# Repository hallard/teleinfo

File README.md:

Update 12.10.2021: Moved APIKEY from url to Authorization Header

Repository dédié à la Téléinformation
=====================================

Ce dossier à la base était pour le programme téléinfo broadcast et emoncms, mais il est devenu au fur et à mesure un peu le fourre tout de mes projets concernant la téléinformation.
Dorénavant, je crée des repos séparés pour les nouveaux projets 

Dans ce repo vous trouverez :
- Le dongle [Micro Teleinfo](https://github.com/hallard/teleinfo/tree/master/MicroTeleinfo) ainsi que les liens vers la documentation
- Le shield Raspberry [Pi PiTinfo](https://github.com/hallard/teleinfo/tree/master/PiTInfo) ainsi que les liens vers la documentation

Et le nouveau projet Teleinfo Wifi Serveur dans un repo dédié
- [WifInfo](https://github.com/hallard/WifInfo)

Historique de ce repo et programme associé ci-dessous :

Téléinfo Broadcast, mySQL et Emoncms
====================================
Ce programme qui permet de récupérer les trames téléinfo reçue par la liaison série d'un ordinateur (ou autre périphérique) puis de les envoyer (broadcaster) sur un reseau local. de ce fait, il est possible de récupérer ces informations sur une 
(ou même plusieurs machines) pour en faire le traitement souhaité.

Il est aussi capable d'envoyer les données de téléinfo vers une base mySQL ou un serveur Emoncms
 
Ce programme fonctionne uniquement sous linux (testé sur Debian Lenny et wheezy) mais çà ne doit pas être sorcier de l'adapter pour Windows.
 
Le fonctionnement est très simple, et peut être distingué en deux modes :
  - Le mode serveur (ou daemon), c'est à dire qu'il ecoute les trames reçues sur le port série et les transfère immediatement via une trame UDP sur le réseau local. Petite subtilité, en fait deux trames identiques sont envoyés, une sur le port 1200 et l'autre sur le port 1201, tout simplement parce que mon PC de domotique utilise deux programmes pour traiter les données de téléinfo or deux programmes distincts ne peuvent pas se écouter (binder) simultanément sur le même port.
  - mon daemon domotique avec l'affichage en temps réél des données téléinfo reçues
  - un script executé toutes les 5 minutes pour envoyer les données de téléinfo sur la base MySQL

  - Le mode client, c'est à dire qu'il écoute sur le réseau local une trame UDP (donc envoyée par de daemon) puis si celle-ci est valide, fait un traitement associé. Dans mon cas, soit on affiche la trame soit on stocke les données dans une base MySQL avec les valeurs reçues (le nom des champs de la table doit être le même que les champs de la trame reçue, donc un champs ADCO, …).

Suivez mes nouveautés et autres projets sur mon [blog][4] 

Installation et configuration
==============================

Tout est documenté sur la page dédié [teleinfo][5] de mon blog 

License
=======

<br /><span xmlns:dct="http://purl.org/dc/terms/" property="dct:title">MicroTeleinfo</span> de <span xmlns:cc="http://creativecommons.org/ns#" property="cc:attributionName">Charles-Henri Hallard</span> est mis à disposition selon les termes de la <a rel="license" href="http://creativecommons.org/licenses/by-nc-sa/4.0/">licence Creative Commons Attribution - Pas d’Utilisation Commerciale - Partage dans les Mêmes Conditions 4.0 International</a>.

[4]: http://hallard.me
[5]: http://hallard.me/teleinfo-emoncms/

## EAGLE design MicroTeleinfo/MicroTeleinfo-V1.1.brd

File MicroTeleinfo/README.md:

Micro Téléinfo
==============
Dongle USB permettant de récupérer les trames téléinformation

Suivez mes nouveautés et autres projets sur mon [blog][4] 

Installation et configuration
==============================

Tout est documenté sur la page dédié [teleinfo][5] de mon blog.

Vous pouvez acheter le montage terminé sur [Tindie][6]

License
=======

<br /><span xmlns:dct="http://purl.org/dc/terms/" property="dct:title">MicroTeleinfo</span> de <span xmlns:cc="http://creativecommons.org/ns#" property="cc:attributionName">Charles-Henri Hallard</span> est mis à disposition selon les termes de la <a rel="license" href="http://creativecommons.org/licenses/by-nc-sa/4.0/">licence Creative Commons Attribution - Pas d’Utilisation Commerciale - Partage dans les Mêmes Conditions 4.0 International</a>.

Conception
==========

Nouvelle version V1.1 avec transistor MOSFET pour une meilleure compatibilité avec les compteurs.

**Schémas V1.1**  

**Circuit Imprimé V1.1**  
&nbsp;&nbsp;

**Schémas V1.0**  

**Circuit Imprimé V1.0**  
&nbsp;&nbsp;

[4]: http://hallard.me
[5]: http://hallard.me/teleinfo/
[6]: https://www.tindie.com/products/Hallard/micro-teleinfo/

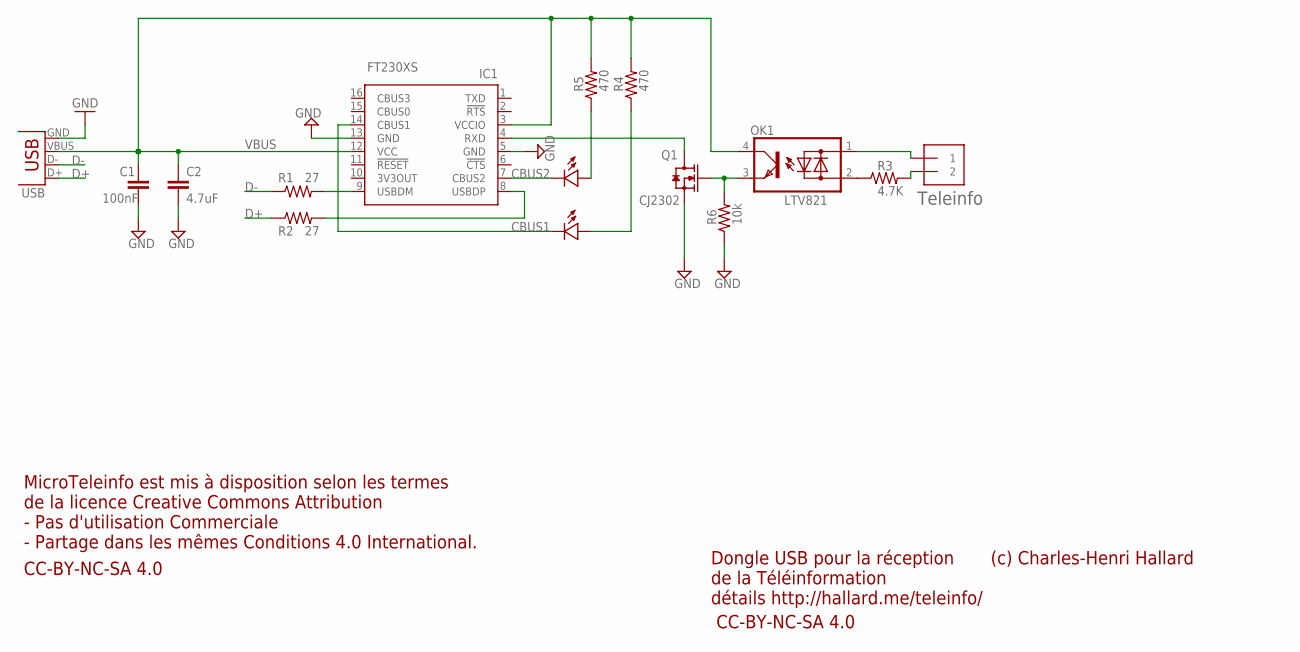
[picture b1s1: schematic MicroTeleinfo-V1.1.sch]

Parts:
C1: 100nF; 0603-CAP
C2: 4.7uF; 0805-CAP
IC1: FT230XS; SSOP16
LED1: Green; 0805-LED
LED2: Red; 0805-LED
OK1: LTV821; DIL4-SMD
Q1: CJ2302; SOT23
R1, R2: 27; 0603-RES
R3: 4.7K; 0805-RES
R4, R5: 470; 0603-RES
R6: 10k; 0603-RES
TELEINFO: 1X2-3.5MM
USB: USBNOSILK; USB-A-H_NO_SILK

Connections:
CBUS1: IC1.14 (CBUS1), LED1.MINUS
CBUS2: IC1.7 (CBUS2), LED2.MINUS
D+: R2.1, USB.D+
D-: R1.1, USB.D-
GND: C1.2, C2.2, IC1.5 (GND), IC1.13 (GND), Q1.2 (S), R6.1, USB.GND
unnamed: OK1.3 (E), Q1.1 (G), R6.2
unnamed: OK1.2 (AC2), R3.1
unnamed: OK1.1 (AC1), TELEINFO.1
unnamed: R3.2, TELEINFO.2
unnamed: LED1.PLUS, R4.1
unnamed: LED2.PLUS, R5.1
unnamed: IC1.4 (RXD), Q1.3 (D)
USBDM: IC1.9 (USBDM), R1.2
USBDP: IC1.8 (USBDP), R2.2
VBUS: C1.1, C2.1, IC1.3 (VCCIO), IC1.12 (VCC), OK1.4 (C), R4.2, R5.2, USB.VBUS

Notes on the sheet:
Dongle USB pour la réception de la Téléinformation détails http://hallard.me/teleinfo/
Teleinfo
CC-BY-NC-SA 4.0
MicroTeleinfo est mis à disposition selon les termes de la licence Creative Commons Attribution - Pas d'utilisation Commerciale - Partage dans les mêmes Conditions 4.0 International.
(c) Charles-Henri Hallard

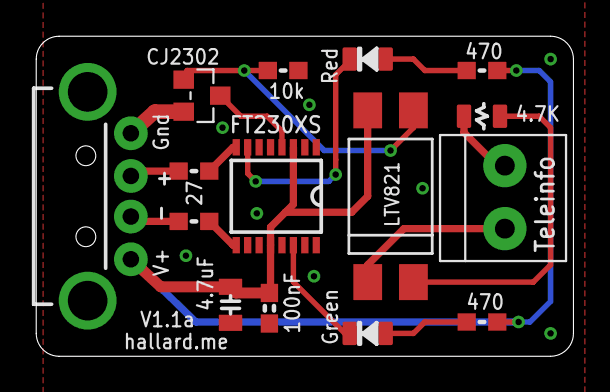
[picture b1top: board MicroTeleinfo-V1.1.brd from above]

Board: 2 copper layers, 29.8 x 17.8 mm, 16 parts (1 on the bottom side), 15 nets.

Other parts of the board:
U$1: LOGO_CH2I_75MM

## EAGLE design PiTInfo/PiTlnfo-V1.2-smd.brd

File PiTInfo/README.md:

Pi Téléinfo
===========

Nouvelle version V1.2 avec l'étage à transistor FET afin de pallier à tout problème de réception de la téléinformation. 

Consulter l'article [dédié][10] sur mon blog.

Installation et configuration
==============================

La led ainsi que le transistor sont au choix (en CMS ou à trous sur la version non SMD) car dans certains boitiers je ne suis pas sur qu'une led 3MM loge, du coup vous avez le choix ou non de l'installer. Vous pouvez ne pas la mettre, c'est facultatif pour le visuel. Si vous ne mettez pas la LED la resistance 470 Ohm ne sert à rien.

Veuillez consulter les articles suivants pour plus d'information

* [Téléinfo, Emoncms avec Node Red sur Raspberry PI][1]
* [Démystifier le décodage Téléinformation et l’optocoupleur SFH6206][8]
* [Teleinfo Broadcast comptatible avec Emoncms][3]
* [Gestion de la Teleinfo avec un Raspberry Pi et une carte ArduiPi][9]

Vous pouvez acheter le montage tout fait sur [Tindie][6] ou sur [Lectronz](https://lectronz.com/products/pitinfo).

Les clients européens peuvent préférer commander sur Lectronz, qui propose des moyens de paiement supplémentaires et des prix en euros.

License
=======

<br /><span xmlns:dct="http://purl.org/dc/terms/" property="dct:title">PiTInfo</span> de <span xmlns:cc="http://creativecommons.org/ns#" property="cc:attributionName">Charles-Henri Hallard</span> est mis à disposition selon les termes de la <a rel="license" href="http://creativecommons.org/licenses/by-nc-sa/4.0/">licence Creative Commons Attribution - Pas d’Utilisation Commerciale - Partage dans les Mêmes Conditions 4.0 International</a>.

Conception
==========

**Schémas V1.2 SMD**  

**Circuit Imprimé V1.2 SMD**  
&nbsp;&nbsp;     

**Schémas V1.2 trous traversants **  

**Circuit Imprimé V1.2 version trous traversants**  
&nbsp;&nbsp;      

Suivez mes nouveautés et autres projets sur mon [blog][4] 

[1]: http://hallard.me/pitinfo/
[2]: http://hallard.me/arduipi-the-shield-that-brings-arduino-to-raspberry-pi/
[3]: http://hallard.me/teleinfo-emoncms/
[4]: http://hallard.me
[5]: http://hallard.me/teleinfo/
[6]: https://www.tindie.com/products/Hallard/pitinfo/
[7]: http://hallard.me/teleinfo/
[8]: http://hallard.me/demystifier-la-teleinfo/
[9]: http://hallard.me/gestion-de-la-teleinfo-avec-un-raspberry-pi-et-une-carte-arduipi/
[10]: http://hallard.me/pitinfov12/

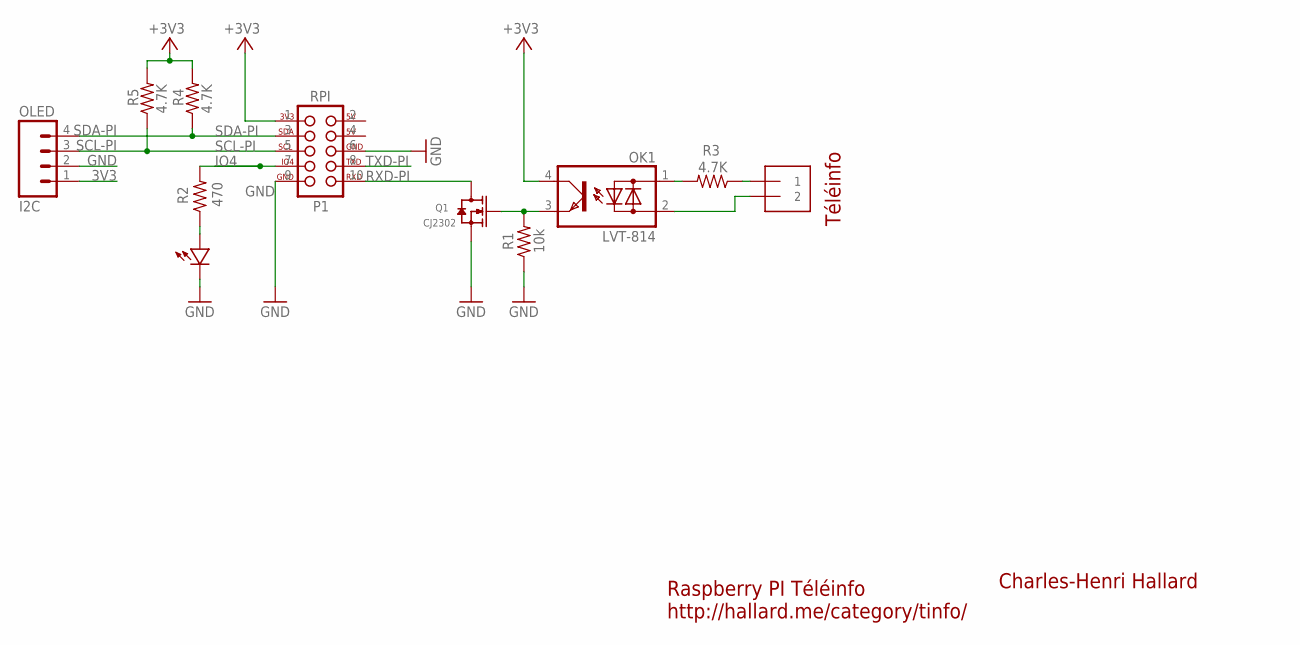
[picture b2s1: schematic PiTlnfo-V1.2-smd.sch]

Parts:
J1: 1X2-3.5MM
LED: LED0805; 0805-LED
OK1: LVT-814; DIL04
OLED: I2C; 1X04_LOCK
Q1: CJ2302; SOT23
R1: 10k; 0805-RES
R2: 470; 0805-RES
R3, R4, R5: 4.7K; 0805-RES
U$2: RASPBERRY_PI_2X5; 2X05_LOCK

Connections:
2: U$2.2
3V3: OK1.4 (C), OLED.1, R4.2, R5.2, U$2.1
4: U$2.4
GND: LED.MINUS, OLED.2, Q1.2 (S), R1.1, U$2.6, U$2.9
IO4: R2.2, U$2.7
unnamed: OK1.3 (E), Q1.1 (G), R1.2
unnamed: LED.PLUS, R2.1
unnamed: J1.2, OK1.2 (AC2)
unnamed: J1.1, R3.1
unnamed: OK1.1 (AC1), R3.2
RXD-PI: Q1.3 (D), U$2.10
SCL-PI: OLED.3, R5.1, U$2.5
SDA-PI: OLED.4, R4.1, U$2.3
TXD-PI: U$2.8

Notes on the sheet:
Raspberry PI Téléinfo http://hallard.me/category/tinfo/
Charles-Henri Hallard
Téléinfo

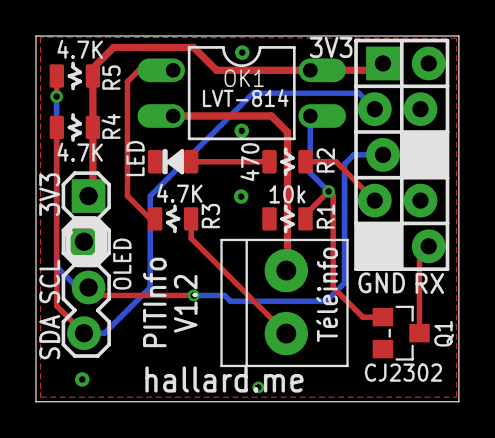
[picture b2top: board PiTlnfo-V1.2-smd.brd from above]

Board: 2 copper layers, 23.5 x 20.3 mm, 12 parts (1 on the bottom side), 11 nets.

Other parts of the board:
U$1: OSHW-LOGO-M

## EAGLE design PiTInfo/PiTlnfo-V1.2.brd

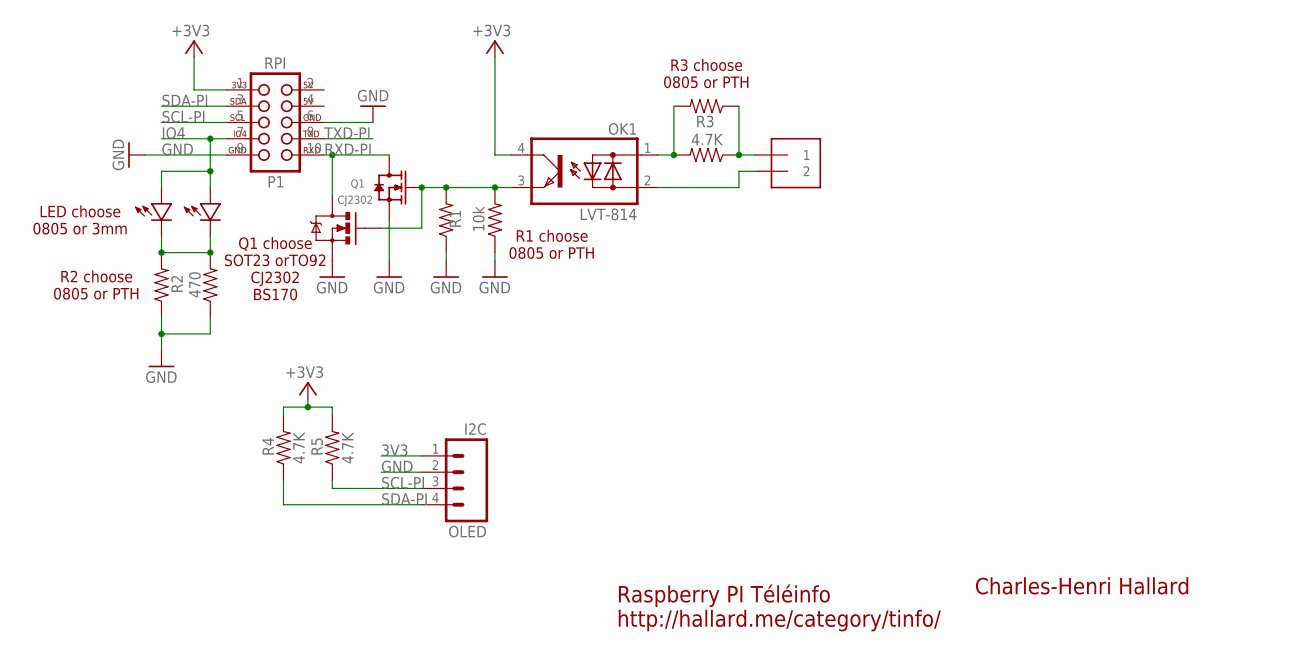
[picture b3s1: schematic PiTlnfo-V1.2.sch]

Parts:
J1: 1X2-3.5MM
LED: LED0805-LARGE; 0805-LED-LARGEPADS
LED3: LED3MM
OK1: LVT-814; DIL04
OLED: I2C; 1X04_LOCK
Q1: CJ2302; SOT23
Q2: MOS-N; TO-92
R1: 10k; 1206-RES
R2: 470; AXIAL-0.3-KIT
R3: 4.7K; AXIAL-0.3-KIT
R4, R5: 4.7K; 0805-RES
R101: 10K; AXIAL-0.3-KIT
R102: 470; 1206-RES
R103: 4.7K; 1206-RES
U$2: RASPBERRY_PI_2X5; 2X05_LOCK

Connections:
2: U$2.2
3V3: OK1.4 (C), OLED.1, R4.2, R5.2, U$2.1
4: U$2.4
GND: OLED.2, Q1.2 (S), Q2.3 (S), R1.1, R2.P$1 (1), R101.P$1 (1), R102.1, U$2.6, U$2.9
IO4: LED.PLUS, LED3.PLUS, U$2.7
unnamed: OK1.3 (E), Q1.1 (G), Q2.2 (G), R1.2, R101.P$2 (2)
unnamed: LED.MINUS, LED3.MINUS, R2.P$2 (2), R102.2
unnamed: J1.2, OK1.2 (AC2)
unnamed: J1.1, R3.P$1 (1), R103.1
unnamed: OK1.1 (AC1), R3.P$2 (2), R103.2
RXD-PI: Q1.3 (D), Q2.1 (D), U$2.10
SCL-PI: OLED.3, R5.1, U$2.5
SDA-PI: OLED.4, R4.1, U$2.3
TXD-PI: U$2.8

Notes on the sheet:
Raspberry PI Téléinfo http://hallard.me/category/tinfo/
Charles-Henri Hallard
R2 choose 0805 or PTH
R3 choose 0805 or PTH
LED choose 0805 or 3mm
R1 choose 0805 or PTH
Q1 choose SOT23 orTO92 CJ2302 BS170

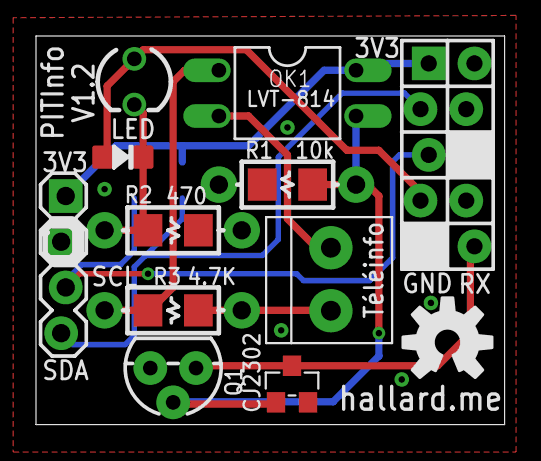
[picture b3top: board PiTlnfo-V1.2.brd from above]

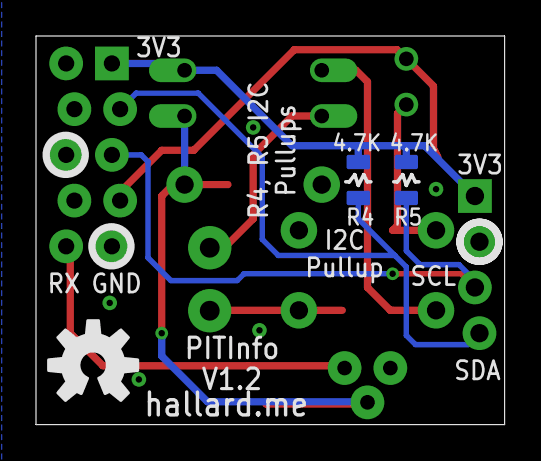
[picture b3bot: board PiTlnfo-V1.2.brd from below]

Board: 2 copper layers, 26.0 x 21.6 mm, 18 parts (3 on the bottom side), 11 nets.

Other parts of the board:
U$1, U$4: OSHW-LOGO-M

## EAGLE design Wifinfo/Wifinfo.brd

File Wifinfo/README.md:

Wifinfo : Wifi Teleinfo server
==============================

This is a server board for Teleinfo French Meter Measure Library, it can be used as a stand alone device web server that can display/send Teleinfo information.

You can see Teleinformation official french datasheet [there][1]

Since this is really dedicated to French energy measuring system, I will continue in French

Pour le moment le logiciel utilisé doit être considéré comme une version béta (voir alpha), même si le hardware est parfaitement fonctionnel, la partie logicielle est loin d'être terminée.

##Fonctionnalités Terminées
- Mise à jour par Wifi (pas besoin de cable) 
- Affichage dans l'interface Web des données de Teleinfo 
- Affichage dans l'interface Web des données système 

##Fonctionnalités à écrire
A terme les fonctionnalités de cette carte seront les suivantes :
- Créer la page WEB de connexion a un Wifi local 
- Créer la page WEB de configuration du Module 
- REST API pour effectuer des reqêtes afin d'obtenir les données de Téléinfo du type http://wifinfo/PAPP pour récupérer le 
contenu de l'étiquette PAPP (par exemple)
- Envoi des données de téléinfo vers EMONCMS
- Envoi des données de téléinfo vers les box domotique (JEEDOM, EEDOMUS, ...)
- D'autres idées arriveront surement en cours de toute...

##Schémas  

##Cartes 
&nbsp;
&nbsp;

##Documentation de la libraire LibTeleinfo
J'ai écrit un article [dédié][10] sur la librairie téléinfo qui est utilisée dans ce module. Vous pouvez aussi voir les [catégories][6] associées à la téléinfo sur mon [blog][7].

Pour les commentaires et le support vous pouvez allez sur le [forum][8] dédié ou dans la [communauté][9] 

##Sketch d'exemples
- [ESP8266_WEB][5] ESP8266 Web dynamic + Rest application, version en cours de développement.

##License
<br /><span xmlns:dct="http://purl.org/dc/terms/" property="dct:title">Wifinfo</span> by <a xmlns:cc="http://creativecommons.org/ns#" href="https://hallard.me/max31865" property="cc:attributionName" rel="cc:attributionURL">Charles-Henri Hallard</a> is licensed under a <a rel="license" href="http://creativecommons.org/licenses/by-nc-sa/4.0/">Creative Commons Attribution-NonCommercial-ShareAlike 4.0 International License</a>.<br />Based on a work at <a xmlns:dct="http://purl.org/dc/terms/" href="https://github.com/hallard/MAX31865-Breakout" rel="dct:source">https://github.com/hallard/teleinfo/tree/master/Wifinfo</a>.

[1]: http://www.erdf.fr/sites/default/files/ERDF-NOI-CPT_02E.pdf
[2]: http://learn.adafruit.com/arduino-tips-tricks-and-techniques/arduino-libraries
[5]: https://github.com/hallard/LibTeleinfo/blob/master/Examples/ESP8266_WEB/ESP8266_WEB.ino
[6]: https://hallard.me/category/tinfo/
[7]: https://hallard.me
[8]: https://community.hallard.me/category/7
[9]: https://community.hallard.me
[10]: https://hallard.me/libteleinfo

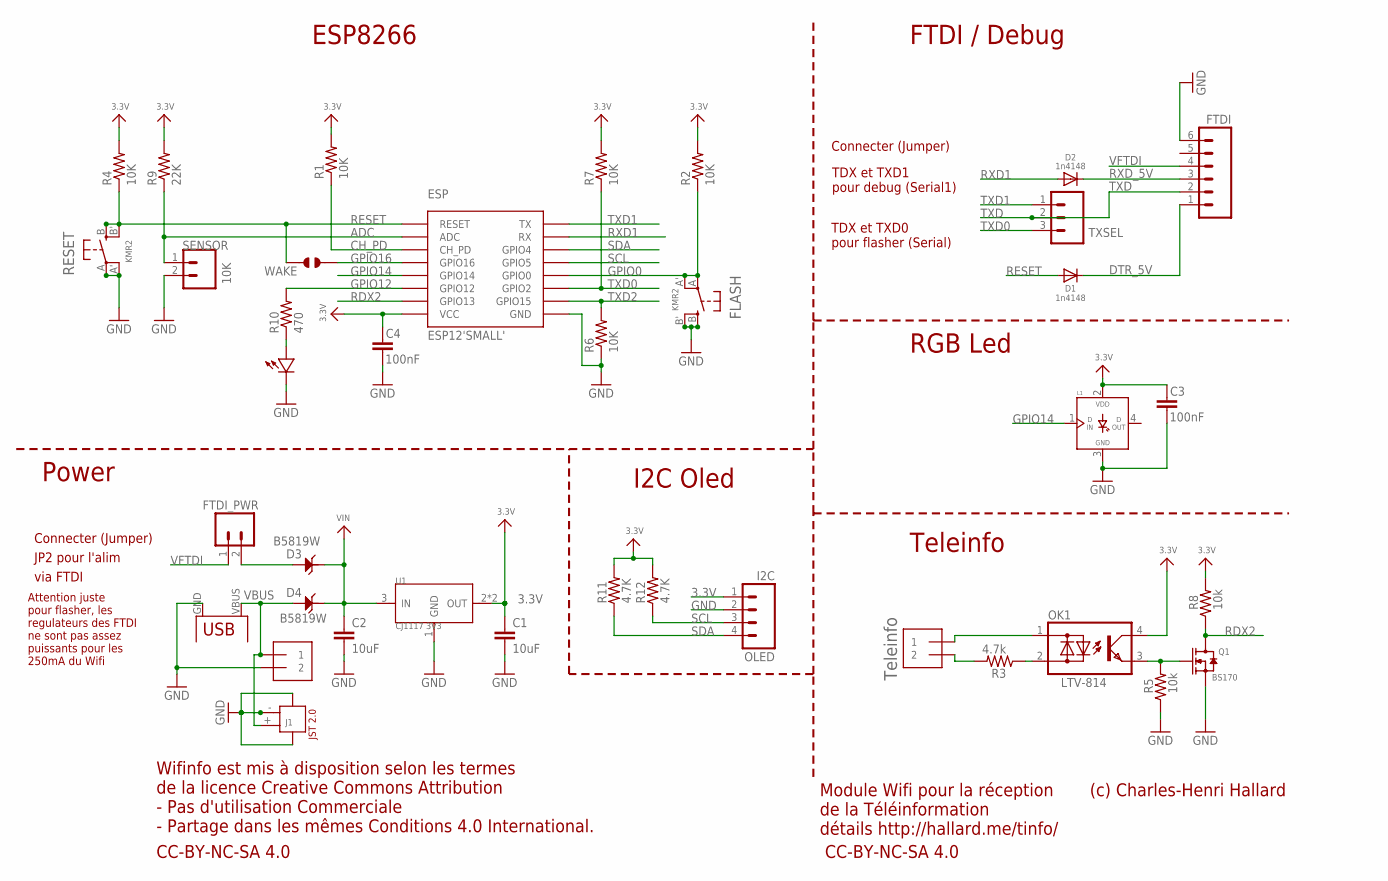
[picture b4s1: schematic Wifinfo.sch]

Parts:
C1, C2: 10uF; 0805-CAP
C3, C4: 100nF; 0603-CAP
D1, D2: 1n4148; SOD-323
D3, D4: B5819W; SOD123-2.7X1.6
ESP: ESP12'SMALL'; ESP08
FLASH: KMR2; BTN_KMR2_4.6X2.8
FTDI: M06SIP_LOCK_NO_SILK; 1X06-SIP_LOCK_NOSILK
FTDI_PWR: M02LOCK; 1X02_LOCK
J1: JST-2P-SMD'2.0'; 2P-SMD-2.0-90D
L1: WS2812B; WS2812-PTH
LED: RED; 0603-LED
OK1: LTV-814; DIL4-SMD
OLED: I2C; 1X04_LOCK
PWR: 1X2-3.5MM
Q1: BS170; SOT23
R1, R2, R4, R6, R7: 10K; 0603-RES
R3: 4.7k; 0603-RES
R5, R8: 10k; 0603-RES
R9: 22K; 0805-RES
R10: 470; 0603-RES
R11, R12: 4.7K; 0603-RES
RESET: KMR2; BTN_KMR2_4.6X2.8
SENSOR: 10K; 1X02
TINFO: 1X2-3.5MM
TXSEL: M03LOCK; 1X03_LOCK
U1: CJ1117 3V3; SOT89
USB: USB; USB_MINIB_POWER
WAKE: JUMPER_SOLDER_1X2

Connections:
3.3V: C1.1, C3.2, C4.2, ESP.VCC, L1.2 (VDD), OK1.4 (C), OLED.1, R1.2, R2.2, R4.2, R7.2, R8.2, R9.2, R11.2, R12.2, U1.2 (OUT), U1.4 (OUT)
ADC: ESP.ADC, R9.1, SENSOR.1
CH_PD: ESP.CH_PD, R1.1
DTR_5V: D1.C, FTDI.1
GND: C1.2, C2.2, C3.1, C4.1, ESP.GND, FLASH.B (S), FLASH.B' (S1), FTDI.6, J1.3, J1.4, J1.- (2), L1.3 (GND), LED.MINUS, OLED.2, PWR.2, Q1.2 (S), R5.1, R6.1, RESET.A, RESET.A' (P1), SENSOR.2, U1.1 (GND), USB.GND
GPIO0: ESP.GPIO0, FLASH.A, FLASH.A' (P1), R2.1
GPIO12: ESP.GPIO12, R10.2
GPIO14: ESP.GPIO14, L1.1 (DIN)
GPIO16: ESP.GPIO16, WAKE.2
unnamed: OK1.3 (E), Q1.1 (G), R5.2
unnamed: D3.1, FTDI_PWR.2
unnamed: OK1.2 (AC2), R3.1
unnamed: OK1.1 (AC1), TINFO.1
unnamed: R3.2, TINFO.2
unnamed: LED.PLUS, R10.1
RDX2: ESP.GPIO13, Q1.3 (D), R8.1
RESET: D1.A, ESP.RESET, R4.1, RESET.B (S), RESET.B' (S1), WAKE.1
RXD1: D2.A, ESP.RX
RXD_5V: D2.C, FTDI.3
SCL: ESP.GPIO5, OLED.3, R12.1
SDA: ESP.GPIO4, OLED.4, R11.1
TXD: FTDI.2, TXSEL.2
TXD0: ESP.GPIO2, R7.1, TXSEL.3
TXD1: ESP.TX, TXSEL.1
TXD2: ESP.GPIO15, R6.2
VBUS: D4.1, J1.+ (1), PWR.1, USB.VBUS (VCC)
VFTDI: FTDI.4, FTDI_PWR.1
VIN: C2.1, D3.2, D4.2, U1.3 (IN)

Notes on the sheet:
Teleinfo
Module Wifi pour la réception de la Téléinformation détails http://hallard.me/tinfo/
CC-BY-NC-SA 4.0
Wifinfo est mis à disposition selon les termes de la licence Creative Commons Attribution - Pas d'utilisation Commerciale - Partage dans les mêmes Conditions 4.0 International.
(c) Charles-Henri Hallard
Power
ESP8266
FTDI / Debug
RGB Led
I2C Oled
TDX et TXD0 pour flasher (Serial)
TDX et TXD1 pour debug (Serial1)
Connecter (Jumper)
JP2 pour l'alim
via FTDI
Attention juste pour flasher, les regulateurs des FTDI ne sont pas assez puissants pour les 250mA du Wifi
JST 2.0

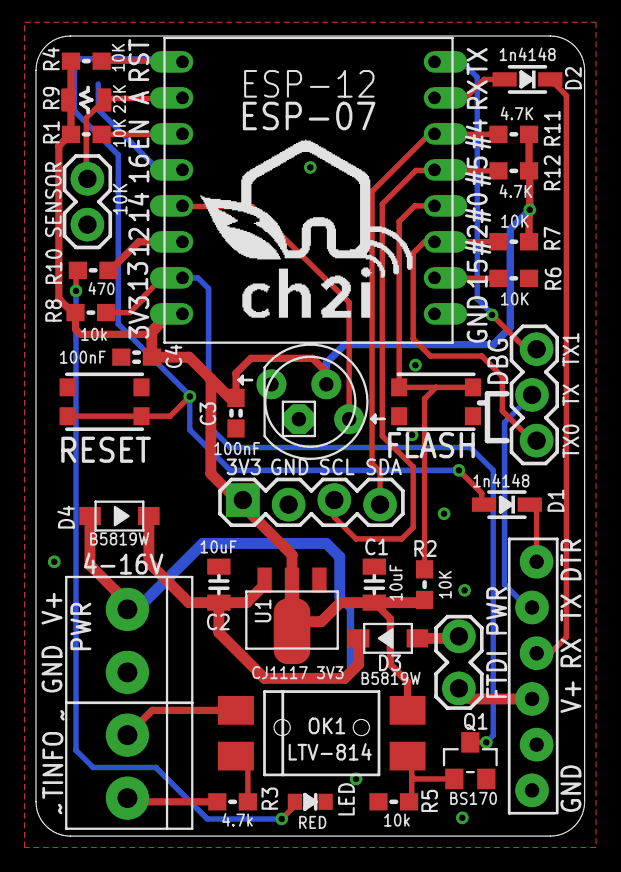
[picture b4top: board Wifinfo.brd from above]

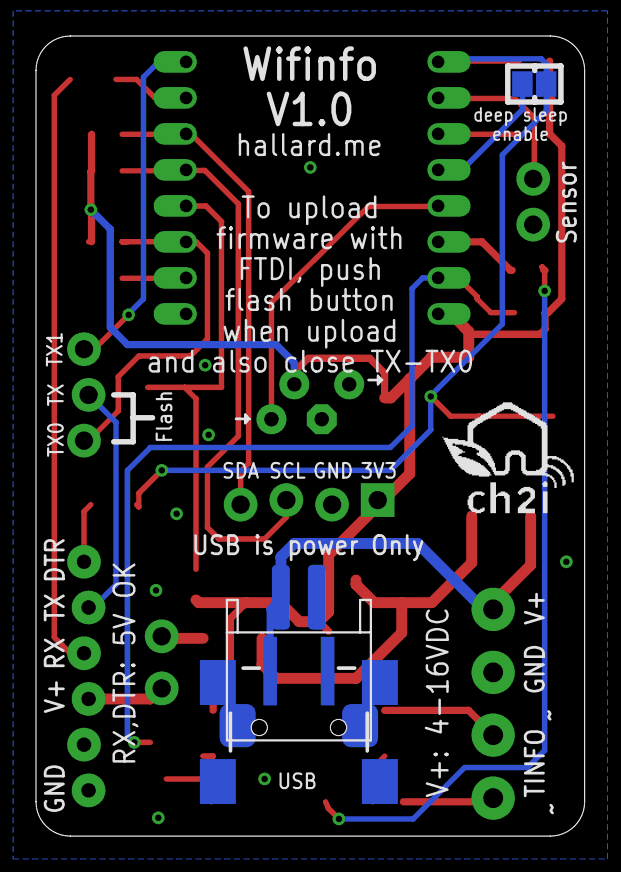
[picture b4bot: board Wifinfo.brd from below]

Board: 2 copper layers, 30.5 x 44.5 mm, 40 parts (4 on the bottom side), 28 nets.

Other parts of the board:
U$11: LOGO_CH2I_110MM
U$12: LOGO_CH2I_75MM

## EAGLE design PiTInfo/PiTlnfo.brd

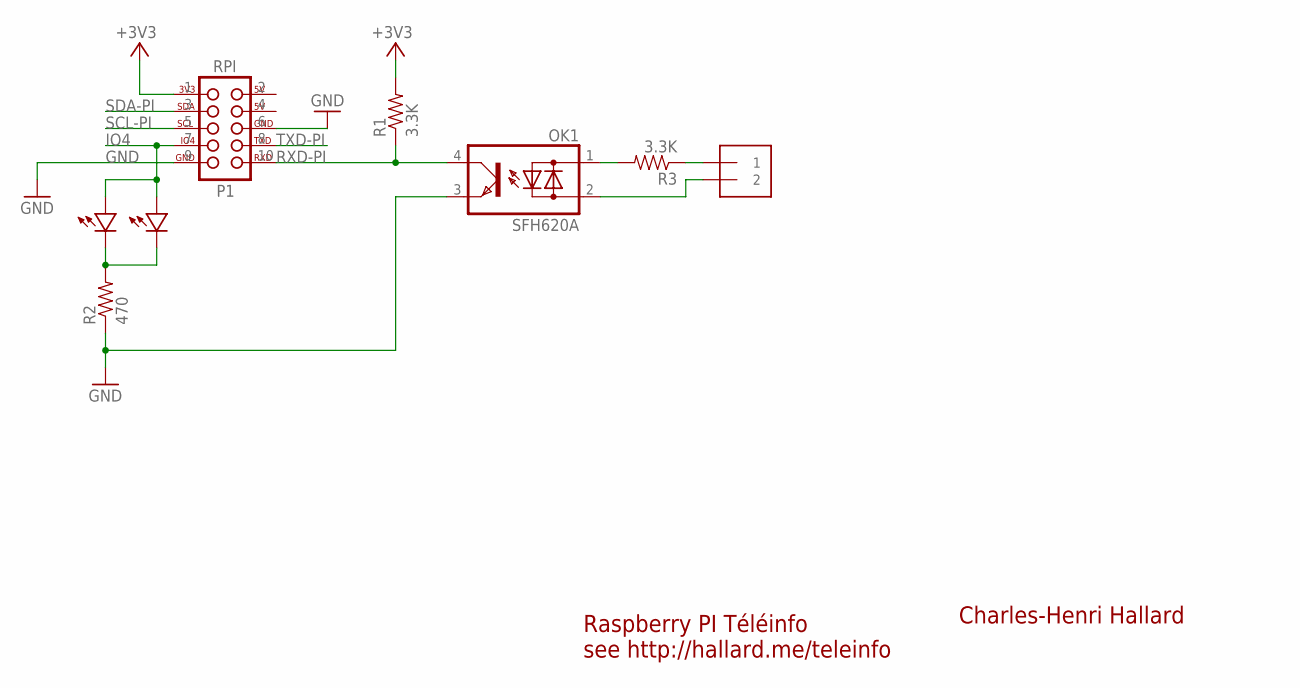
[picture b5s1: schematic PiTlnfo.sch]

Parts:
J1: 1X2-3.5MM
LED1: LED0805-LARGE; 0805-LED-LARGEPADS
LED3: LED3MM
OK1: SFH620A; DIL04
R1, R3: 3.3K; AXIAL-0.3-KIT
R2: 470; AXIAL-0.3-KIT
U$2: RASPBERRY_PI_2X5; 2X05_LOCK

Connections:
2: U$2.2
4: U$2.4
+3V3: R1.P$2 (2), U$2.1
GND: OK1.3 (E), R2.P$1 (1), U$2.6, U$2.9
IO4: LED1.PLUS, LED3.PLUS, U$2.7
unnamed: LED1.MINUS, LED3.MINUS, R2.P$2 (2)
unnamed: J1.2, OK1.2 (AC2)
unnamed: J1.1, R3.P$1 (1)
unnamed: OK1.1 (AC1), R3.P$2 (2)
RXD-PI: OK1.4 (C), R1.P$1 (1), U$2.10
SCL-PI: U$2.5
SDA-PI: U$2.3
TXD-PI: U$2.8

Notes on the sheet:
Raspberry PI Téléinfo see http://hallard.me/teleinfo
Charles-Henri Hallard

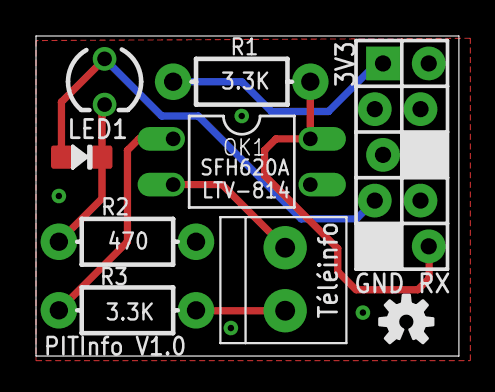
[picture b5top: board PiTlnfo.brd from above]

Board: 2 copper layers, 23.5 x 17.8 mm, 10 parts (1 on the bottom side), 8 nets.

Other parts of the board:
U$1: OSHW-LOGO-M
U$3: OSHW-LOGO-S

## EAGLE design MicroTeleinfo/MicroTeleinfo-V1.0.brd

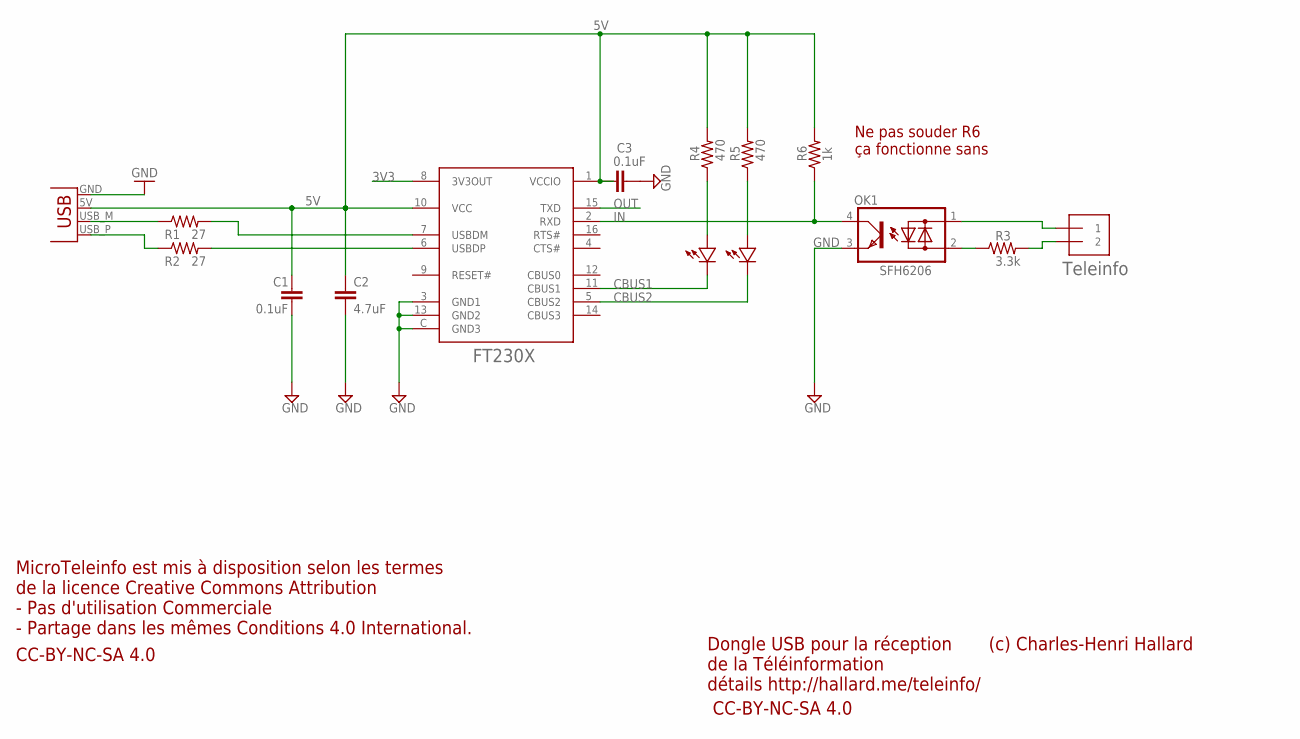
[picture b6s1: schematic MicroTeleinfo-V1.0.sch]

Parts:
C1, C3: 0.1uF; 0603-CAP
C2: 4.7uF; 0805-CAP
FT230X: SERIAL_FT230XQ; SERIAL_QFN4X4-16
LED1: Green; 0805-LED
LED2: Red; 0805-LED
OK1: SFH6206; DIL4-SMD
R1, R2: 27; 0603-RES
R3: 3.3k; 0805-RES
R4, R5: 470; 0603-RES
R6: 1k; 0603-RES
TELEINFO: 1X2-3.5MM
X1: USBPCB; USB-A-PCB

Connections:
3V3: FT230X.8 (3V3OUT)
5V: C1.1, C2.1, C3.1, FT230X.1 (VCCIO), FT230X.10 (VCC), R4.2, R5.2, R6.2, X1.5V (VBUS)
CBUS1: FT230X.11 (CBUS1), LED1.MINUS
CBUS2: FT230X.5 (CBUS2), LED2.MINUS
D+: R2.1, X1.USB_P (D+)
GND: C1.2, C2.2, C3.2, FT230X.3 (GND1), FT230X.13 (GND2), FT230X.C (GND3), OK1.3 (E), X1.GND
IN: FT230X.2 (RXD), OK1.4 (C), R6.1
unnamed: R1.1, X1.USB_M (D-)
unnamed: OK1.2 (AC2), R3.1
unnamed: OK1.1 (AC1), TELEINFO.1
unnamed: R3.2, TELEINFO.2
unnamed: LED1.PLUS, R4.1
unnamed: LED2.PLUS, R5.1
OUT: FT230X.15 (TXD)
USBDM: FT230X.7 (USBDM), R1.2
USBDP: FT230X.6 (USBDP), R2.2

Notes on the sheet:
Dongle USB pour la réception de la Téléinformation détails http://hallard.me/teleinfo/
Teleinfo
CC-BY-NC-SA 4.0
MicroTeleinfo est mis à disposition selon les termes de la licence Creative Commons Attribution - Pas d'utilisation Commerciale - Partage dans les mêmes Conditions 4.0 International.
Ne pas souder R6 ça fonctionne sans
(c) Charles-Henri Hallard

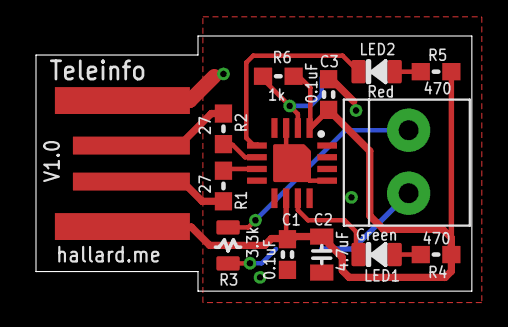
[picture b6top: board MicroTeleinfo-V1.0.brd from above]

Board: 2 copper layers, 24.2 x 14.2 mm, 15 parts (1 on the bottom side), 14 nets.

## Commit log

2012-10-12 Description
2012-10-12 Update Makefile
2013-02-28 Ajout d'un mode test
    Ajout d'un mode test, pour affichage en direct des trame reçues sans
    envoyer de broadcast ou analyser une trame reçue sur le réseau
    switch -m t
2014-05-15 Version 1.07
    Changement de l'interfaçage de la ligne de commande
    Ajout d'un fichier de configuration
    Ajout d'envoi des données vers emoncms
2014-05-15 Added some comments
2014-05-15 Correction #define
2014-05-15 Converted Tab to Spaces
2014-05-15 Correction Erreur de Typo
2014-06-03 Fix some warning for openwrt compilation
2014-06-10 Version 1.08 -> 1.0.8
    Changed version number to be more compliant with openwrt feeds
2014-12-22 Création
2014-12-22 Ajustement des liens
2014-12-22 Correction des liens
2014-12-23 Full French
2015-01-25 Ajout Test
2015-01-25 Correction liens
2015-01-25 Correction Lien
2015-01-25 Ajout d'explications
2015-01-25 Déplacement de section
2015-04-16 Mise à jour après tests
2015-05-19 Ajout lien Tindie
2015-07-20 Creation
2015-07-20 Correction
2015-07-25 Moved to it own repo
2015-07-25 Ajout explications contenu repo
2015-07-25 Ajout descriptions
2015-10-12 MAJ Version 1.2
2015-10-12 Mise en forme
2016-02-20 Ajout V1.1
2016-02-20 Correction VCC IO
2016-02-20 Correction lien image
2021-10-12 fixed APIKEY by moving it to authorization header
2022-10-03 Fix error issue when posting to emoncms if collected data contains unwanted values
2022-10-03 Fix charset encoding
2022-11-23 Update teleinfo.c
    support DEMAIN
2026-04-26 docs(PiTInfo): add Lectronz and Tindie badges
2026-04-29 Add CC BY-NC-SA 4.0 LICENSE file
2026-04-29 license: use pure CC BY-NC-SA 4.0 text for GitHub auto-detection
2026-04-29 license: add copyright header above CC BY-NC-SA 4.0 text

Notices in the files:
parts and their libraries:
SparkFun: Licensing: CC v3.0 Share-Alike You are welcome to use this library for commercial purposes.
SparkFun-Connectors: Licensing: Creative Commons ShareAlike 4.0 International - https://creativecommons.org/licenses/by-sa/4.0
